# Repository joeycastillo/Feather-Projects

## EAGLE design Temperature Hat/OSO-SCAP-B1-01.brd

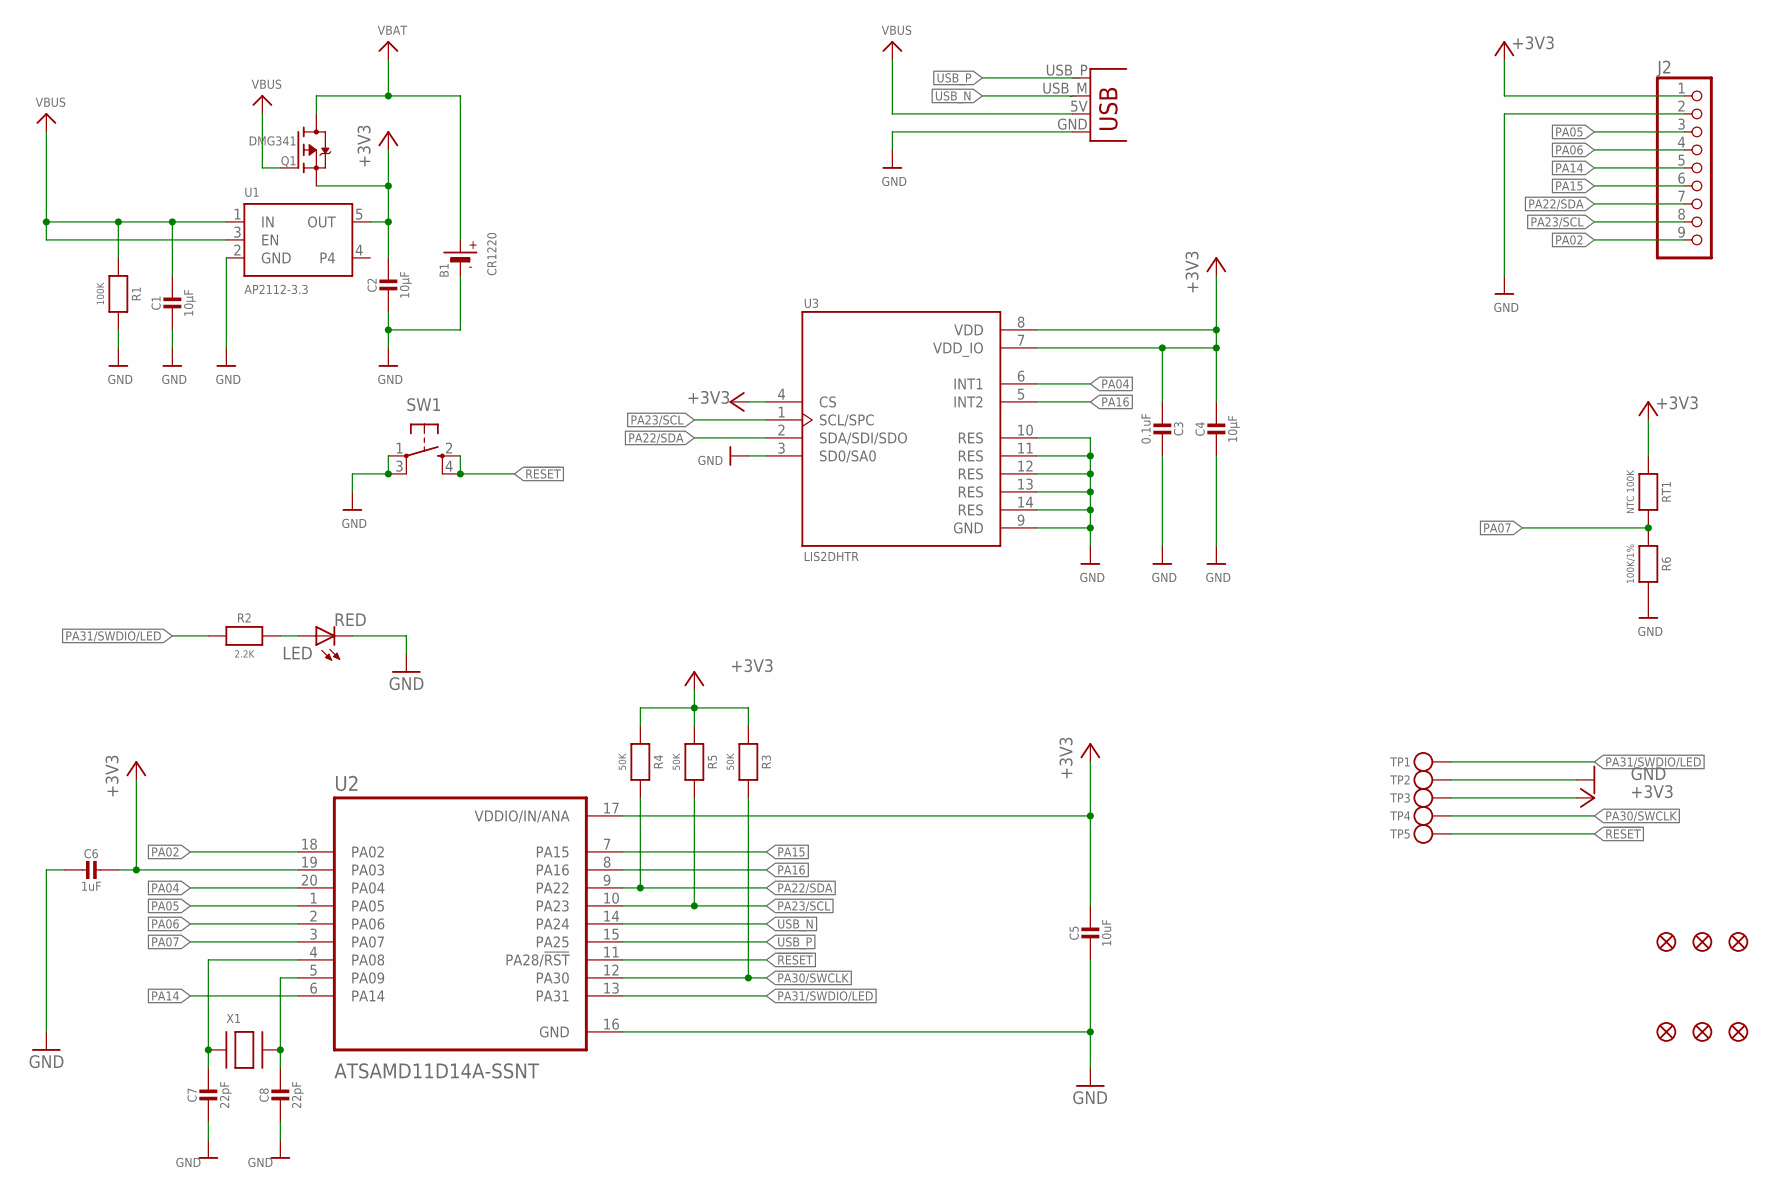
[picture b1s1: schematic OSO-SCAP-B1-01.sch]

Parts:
B1: CR1220
C1, C2, C4: 10µF; 0805-NO
C3: 0.1uF; 0805-NO
C5: 10uF; 0805-NO
C6: 1uF; 0805-NO
C7, C8: 22pF; 0805-NO
FID1, FID2, FID3, FID4, FID5, FID6: FIDUCIAL_1MM
J1: USBPCB; USB-A-PCB
J2: HEADER-1X9_JSTSH; JST_SH9
LED: RED; CHIP-LED0805
Q1: DMG341; SOT23-R
R1: 100K; 0805-NO
R2: 2.2K; 0805-NO
R3, R4, R5: 50K; 0805-NO
R6: 100K/1%; 0805-NO
RT1: NTC 100K; 0805-NO
SW1: SPST_TACT-KMR2; KMR2
TP1, TP2, TP3, TP4, TP5: TESTPOINTROUND2MMNO; TESTPOINT_ROUND_2MM_NO
U1: AP2112-3.3; SOT23-5
U2: ATSAMD11D14A-SSNT; SOIC127P1030X265-20N
U3: LIS2DHTR; PQFN35P200X200X100-14N
X1: XTAL-3.2X1.5; XTAL3215

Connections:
!RESET: SW1.2 (S), SW1.4 (S1), TP5.P$1, U2.11 (PA28/!RST)
+3V3: C2.1, C3.2, C4.1, C5.1, C6.1, J2.1, Q1.2 (S), R3.1, R4.1, R5.1, RT1.1, TP3.P$1, U1.5 (OUT), U2.17 (VDDIO/IN/ANA), U2.19 (PA03), U3.4 (CS), U3.7 (VDD_IO), U3.8 (VDD)
GND: B1.-, C1.2, C2.2, C3.1, C4.2, C5.2, C6.2, C7.2, C8.2, J1.GND, J2.2, LED.C, R1.2, R6.2, SW1.1, SW1.3 (P1), TP2.P$1, U1.2 (GND), U2.16 (GND), U3.3 (SD0/SA0), U3.9 (GND), U3.10 (RES), U3.11 (RES), U3.12 (RES), U3.13 (RES), U3.14 (RES)
unnamed: LED.A, R2.2
PA02: J2.9, U2.18 (PA02)
PA04: U2.20 (PA04), U3.6 (INT1)
PA05: J2.3, U2.1 (PA05)
PA06: J2.4, U2.2 (PA06)
PA07: R6.1, RT1.2, U2.3 (PA07)
PA14: J2.5, U2.6 (PA14)
PA15: J2.6, U2.7 (PA15)
PA16: U2.8 (PA16), U3.5 (INT2)
PA22/SDA: J2.7, R4.2, U2.9 (PA22), U3.2 (SDA/SDI/SDO)
PA23/SCL: J2.8, R5.2, U2.10 (PA23), U3.1 (SCL/SPC)
PA30/SWCLK: R3.2, TP4.P$1, U2.12 (PA30)
PA31/SWDIO/LED: R2.1, TP1.P$1, U2.13 (PA31)
USB_N: J1.USB_M (D-), U2.14 (PA24)
USB_P: J1.USB_P (D+), U2.15 (PA25)
VBAT: B1.+$1 (+), B1.+$2 (+), Q1.3 (D)
VBUS: C1.1, J1.5V (VBUS), Q1.1 (G), R1.1, U1.1 (IN), U1.3 (EN)
XIN32: C7.1, U2.4 (PA08), X1.P$1
XOUT32: C8.1, U2.5 (PA09), X1.P$2

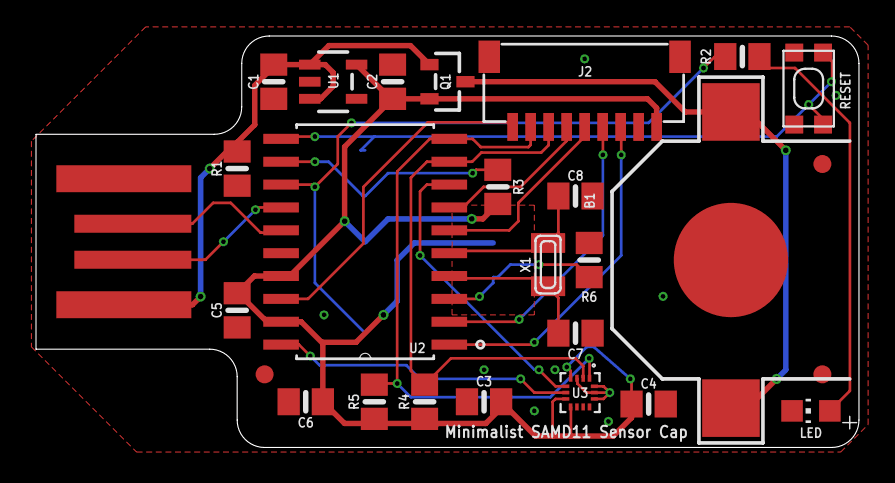
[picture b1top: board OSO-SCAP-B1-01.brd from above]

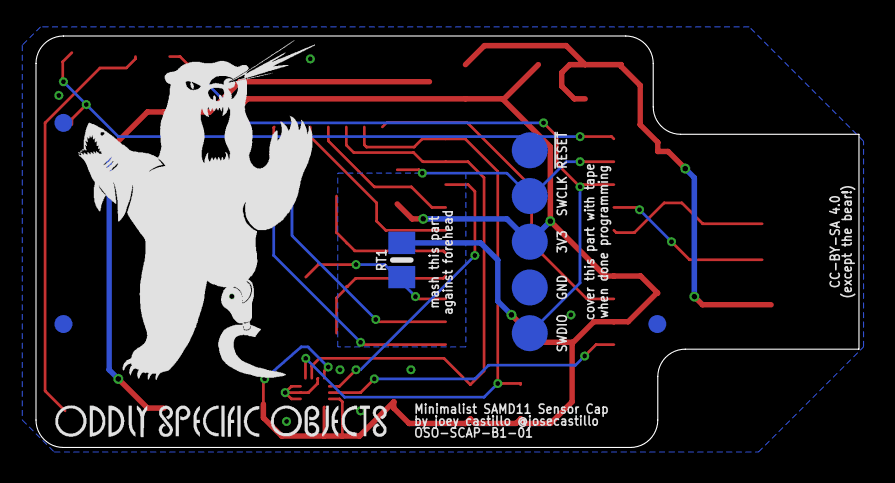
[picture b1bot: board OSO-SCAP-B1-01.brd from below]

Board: 2 copper layers, 45.7 x 22.9 mm, 38 parts (11 on the bottom side), 22 nets.

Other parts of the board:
U$16: OSO_BEAR_525X750MIL_1000DPI
U$21: OSO_WORDMARK_ONELINE_725MIL_1000DPI

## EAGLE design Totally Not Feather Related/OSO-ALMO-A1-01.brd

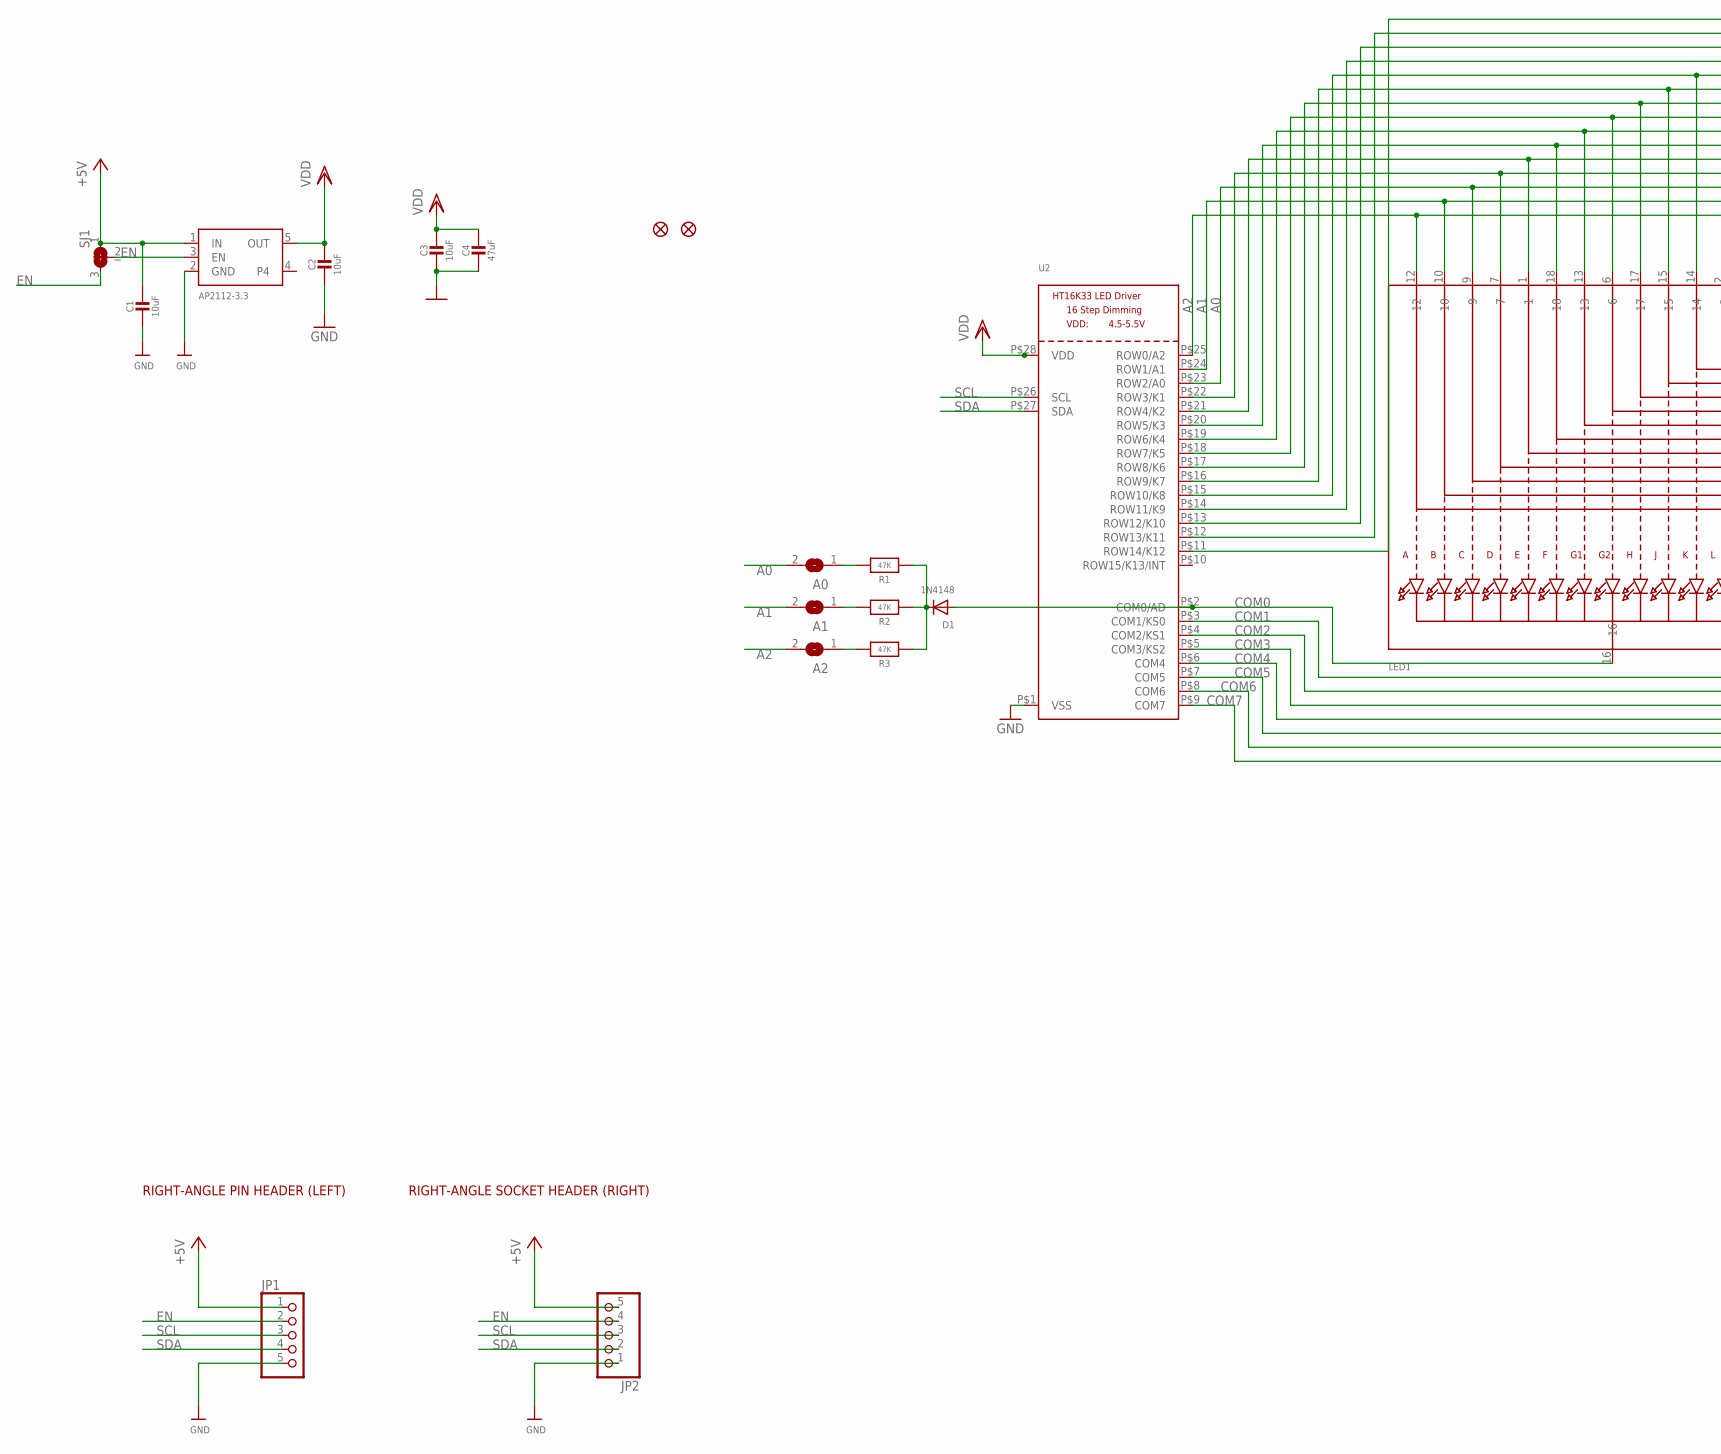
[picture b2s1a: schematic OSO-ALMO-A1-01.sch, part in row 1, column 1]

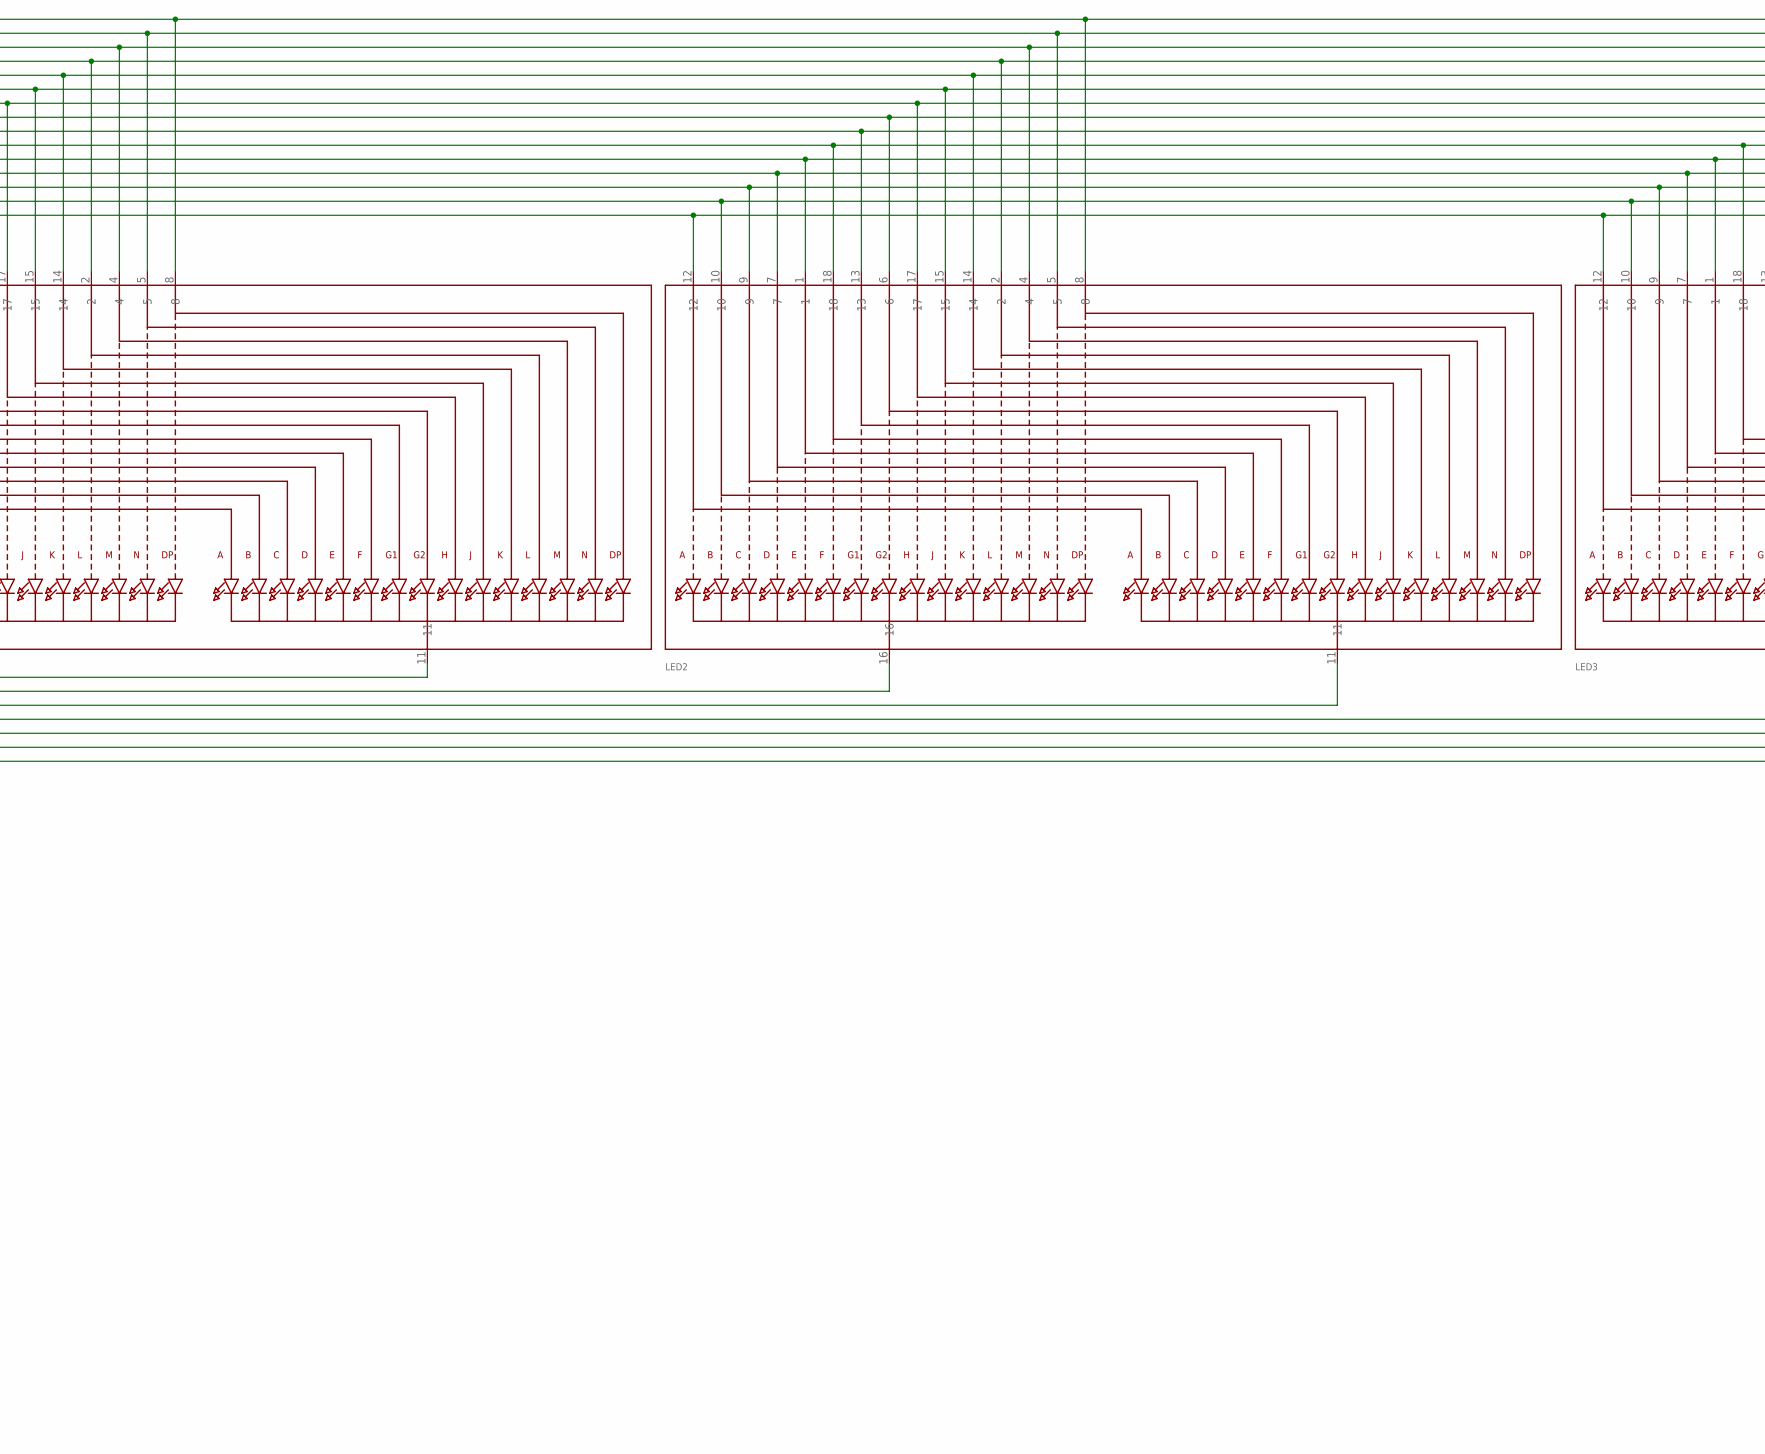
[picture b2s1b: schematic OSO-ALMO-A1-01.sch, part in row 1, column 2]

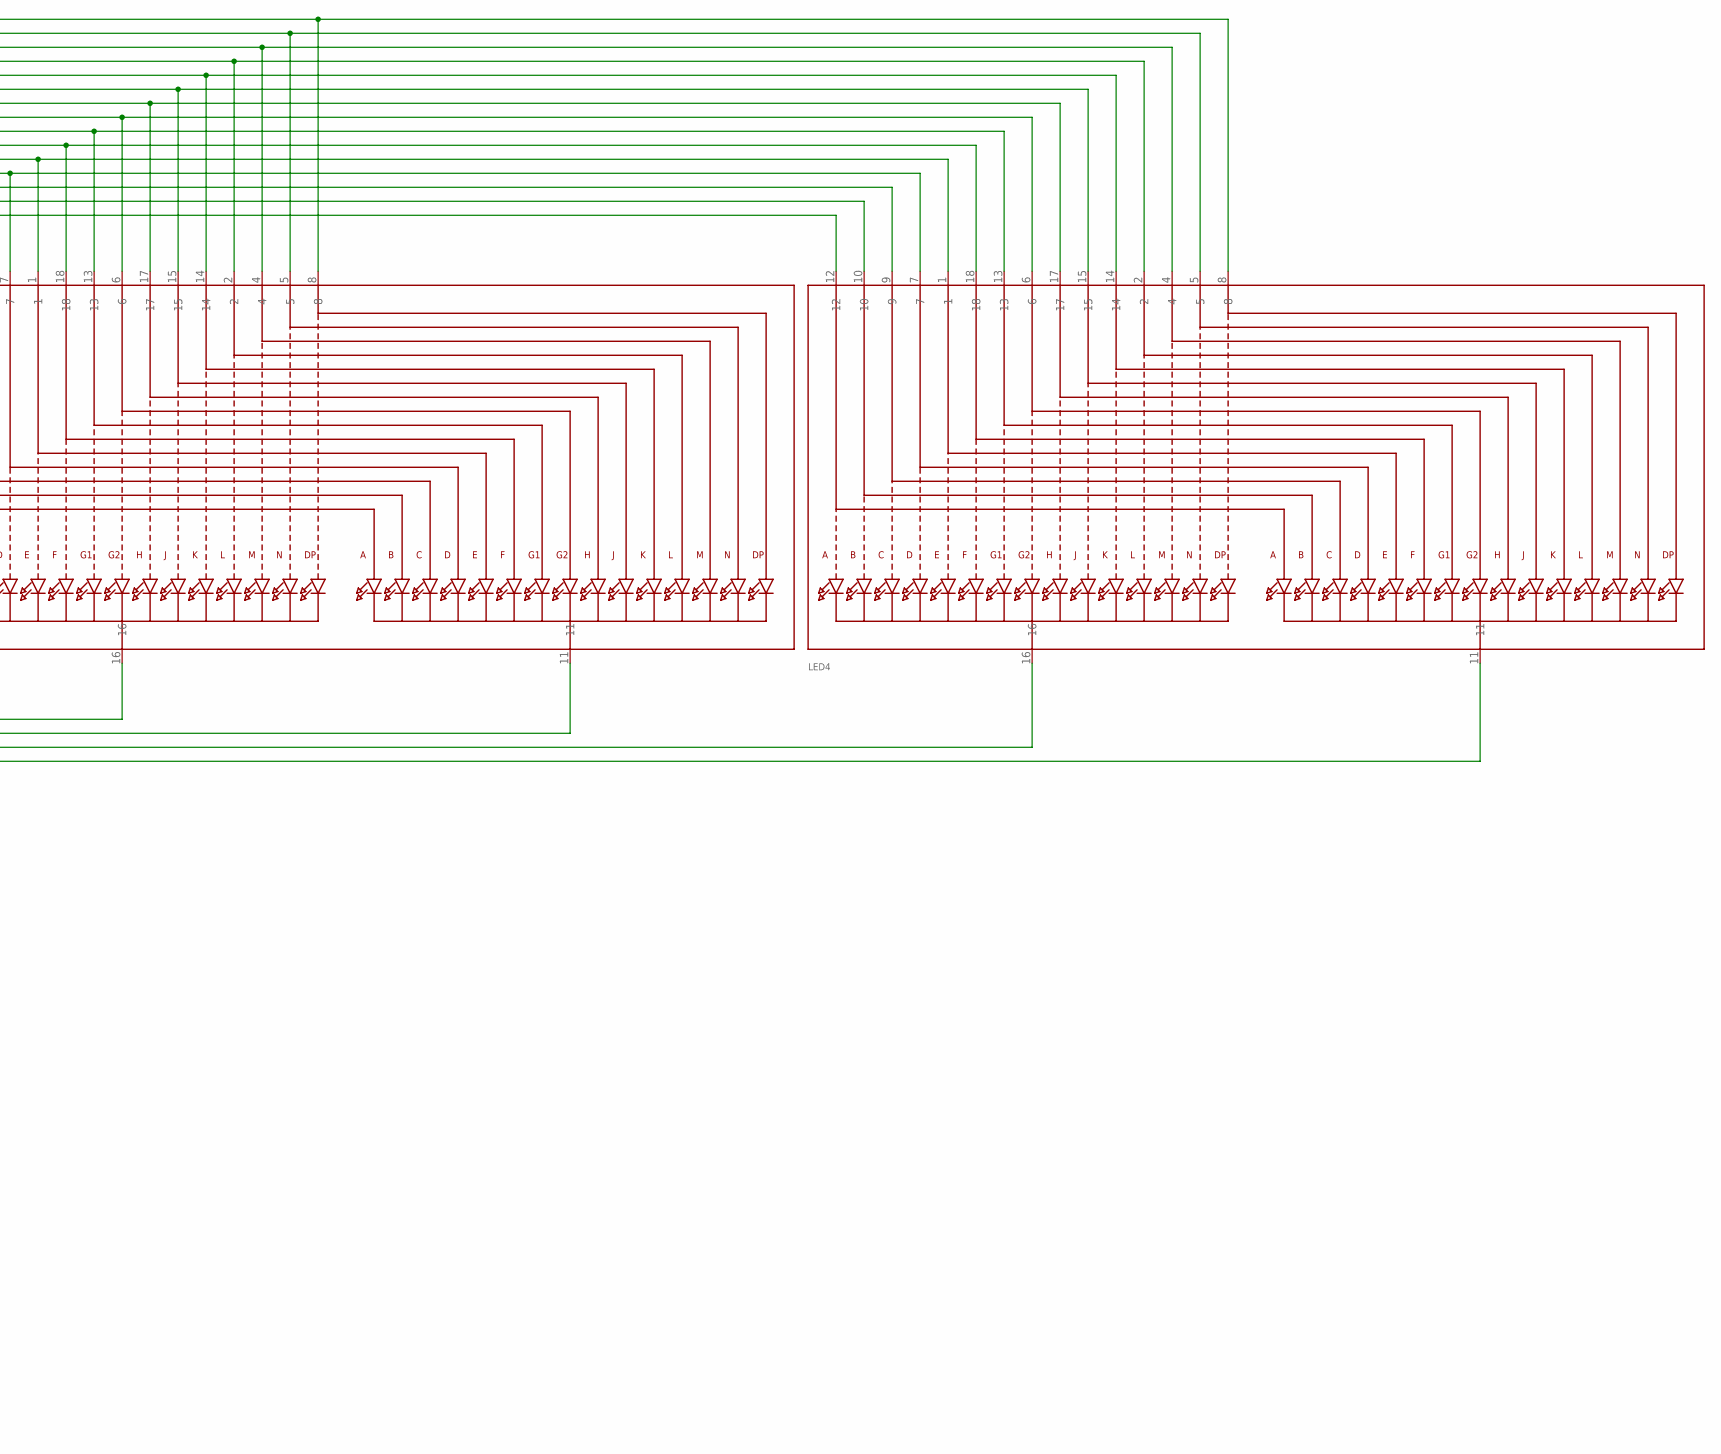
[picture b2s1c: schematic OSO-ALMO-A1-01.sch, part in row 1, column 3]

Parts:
A0, A1, A2: SOLDERJUMPERREFLOW_NOPASTE; SOLDERJUMPER_REFLOW_NOPASTE
C1, C2, C3: 10uF; 0805-NO
C4: 47uF; 0805-NO
D1: 1N4148; SOD-123FL
JP1, JP2: PINHD-1X5/90; 1X05/90
LED1, LED2, LED3, LED4: DISP_SEGMENT_STARBURST_DUAL_COMMONCATHODE; SEGMENT_STARTBUST_DUAL_KWA-541CBB
R1, R2, R3: 47K; 0805-NO
SJ1: SOLDERJUMPER_2WAY; SOLDERJUMPER_2WAY_OPEN_NOPASTE
U1: AP2112-3.3; SOT23-5
U2: HT16K33_SOP28_SKINNY; SOP28_300MIL_SKINNY
U$1, U$2: FIDUCIAL""; FIDUCIAL_1MM

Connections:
+5V: C1.1, JP1.1, JP2.5, SJ1.1, U1.1 (IN)
A0: A0.2, LED1.9, LED2.9, LED3.9, LED4.9, U2.P$23 (ROW2/A0)
A1: A1.2, LED1.10, LED2.10, LED3.10, LED4.10, U2.P$24 (ROW1/A1)
A2: A2.2, LED1.12, LED2.12, LED3.12, LED4.12, U2.P$25 (ROW0/A2)
COM0: D1.A, LED1.16, U2.P$2 (COM0/AD)
COM1: LED1.11, U2.P$3 (COM1/KS0)
COM2: LED2.16, U2.P$4 (COM2/KS1)
COM3: LED2.11, U2.P$5 (COM3/KS2)
COM4: LED3.16, U2.P$6 (COM4)
COM5: LED3.11, U2.P$7 (COM5)
COM6: LED4.16, U2.P$8 (COM6)
COM7: LED4.11, U2.P$9 (COM7)
EN: JP1.2, JP2.4, SJ1.3
GND: C1.2, C2.2, C3.2, C4.2, JP1.5, JP2.1, U1.2 (GND), U2.P$1 (VSS)
unnamed: D1.C, R1.1, R2.1, R3.1
unnamed: LED1.17, LED2.17, LED3.17, LED4.17, U2.P$17 (ROW8/K6)
unnamed: LED1.15, LED2.15, LED3.15, LED4.15, U2.P$16 (ROW9/K7)
unnamed: LED1.14, LED2.14, LED3.14, LED4.14, U2.P$15 (ROW10/K8)
unnamed: A2.1, R3.2
unnamed: LED1.2, LED2.2, LED3.2, LED4.2, U2.P$14 (ROW11/K9)
unnamed: LED1.4, LED2.4, LED3.4, LED4.4, U2.P$13 (ROW12/K10)
unnamed: LED1.7, LED2.7, LED3.7, LED4.7, U2.P$22 (ROW3/K1)
unnamed: LED1.1, LED2.1, LED3.1, LED4.1, U2.P$21 (ROW4/K2)
unnamed: LED1.18, LED2.18, LED3.18, LED4.18, U2.P$20 (ROW5/K3)
unnamed: LED1.13, LED2.13, LED3.13, LED4.13, U2.P$19 (ROW6/K4)
unnamed: LED1.5, LED2.5, LED3.5, LED4.5, U2.P$12 (ROW13/K11)
unnamed: LED1.8, LED2.8, LED3.8, LED4.8, U2.P$11 (ROW14/K12)
unnamed: LED1.6, LED2.6, LED3.6, LED4.6, U2.P$18 (ROW7/K5)
unnamed: A1.1, R2.2
unnamed: A0.1, R1.2
SCL: JP1.3, JP2.3, U2.P$26 (SCL)
SDA: JP1.4, JP2.2, U2.P$27 (SDA)
VDD: C2.1, C3.1, C4.1, U1.5 (OUT), U2.P$28 (VDD)
_EN: SJ1.2, U1.3 (EN)

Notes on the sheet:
RIGHT-ANGLE PIN HEADER (LEFT)
RIGHT-ANGLE SOCKET HEADER (RIGHT)

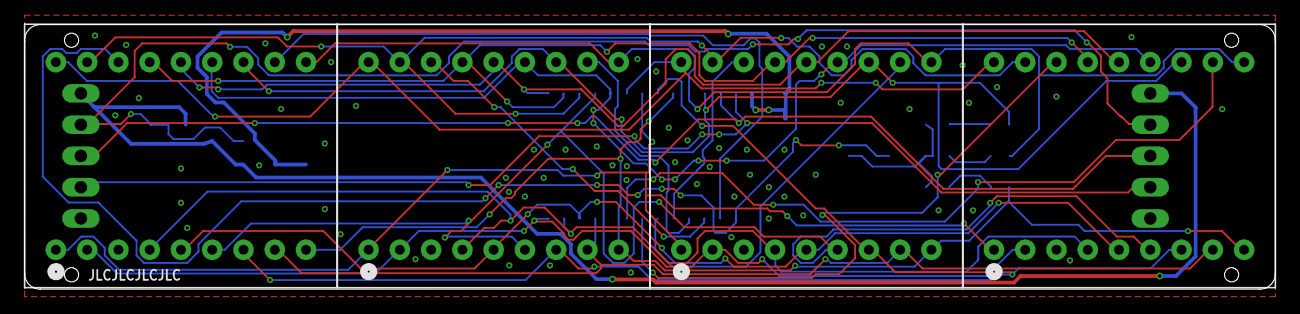
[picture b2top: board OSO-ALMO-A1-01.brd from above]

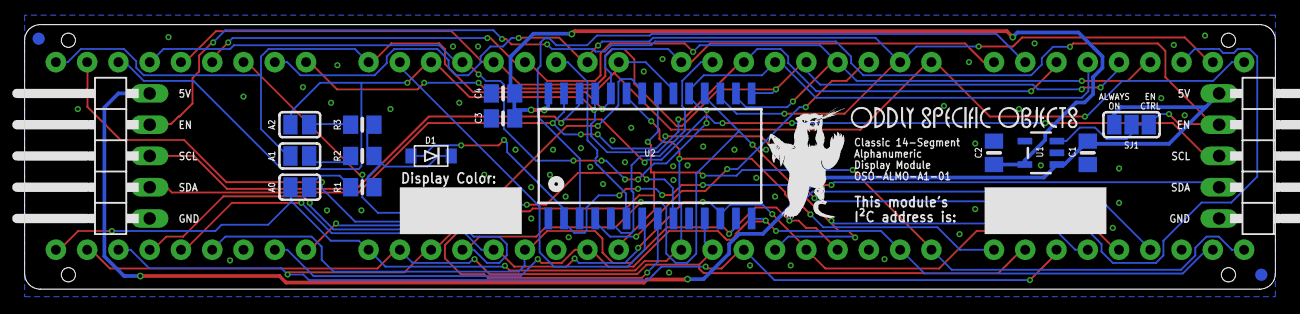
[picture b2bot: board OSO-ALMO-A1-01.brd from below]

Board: 2 copper layers, 101.6 x 21.5 mm, 24 parts (20 on the bottom side), 34 nets.

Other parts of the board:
U$3: OSO_WORDMARK_ONELINE_725MIL_1000DPI
U$6: OSO_BEAR_250X360MIL_1000DPI

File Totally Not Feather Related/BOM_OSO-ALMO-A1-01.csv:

"Qty";"Value";"Device";"Package";"Parts";"Description";"BOM";
"4";"";"DISP_SEGMENT_STARBURST_DUAL_COMMONCATHODE";"SEGMENT_STARTBUST_DUAL_KWA-541CBB";"LED1, LED2, LED3, LED4";"2 x Starburst Segment Displays - Common Cathode";"";
"1";"";"HT16K33_SOP28_SKINNY";"SOP28_300MIL_SKINNY";"U2";"";"";
"2";"";"PINHD-1X5/90";"1X05/90";"JP1, JP2";"PIN HEADER";"";
"3";"";"SOLDERJUMPERREFLOW_NOPASTE";"SOLDERJUMPER_REFLOW_NOPASTE";"A0, A1, A2";"SMD Solder JUMPER";"";
"1";"";"SOLDERJUMPER_2WAY";"SOLDERJUMPER_2WAY_OPEN_NOPASTE";"SJ1";"2-Way Solder Jumper";"";
"3";"10uF";"CAP_CERAMIC0805-NOOUTLINE";"0805-NO";"C1, C2, C3";"Ceramic Capacitors";"";
"1";"1N4148";"DIODE_SOD-123FL";"SOD-123FL";"D1";"Diode";"";
"3";"47K";"RESISTOR0805_NOOUTLINE";"0805-NO";"R1, R2, R3";"Resistors";"";
"1";"47uF";"CAP_CERAMIC0805-NOOUTLINE";"0805-NO";"C4";"Ceramic Capacitors";"";
"1";"AP2112-3.3";"VREG_SOT23-5";"SOT23-5";"U1";"SOT23-5 Fixed Voltage Regulators";"";
"2";"FIDUCIAL""";"FIDUCIAL""";"FIDUCIAL_1MM";"U$1, U$2";"Fiducial Alignment Points";"EXCLUDE";

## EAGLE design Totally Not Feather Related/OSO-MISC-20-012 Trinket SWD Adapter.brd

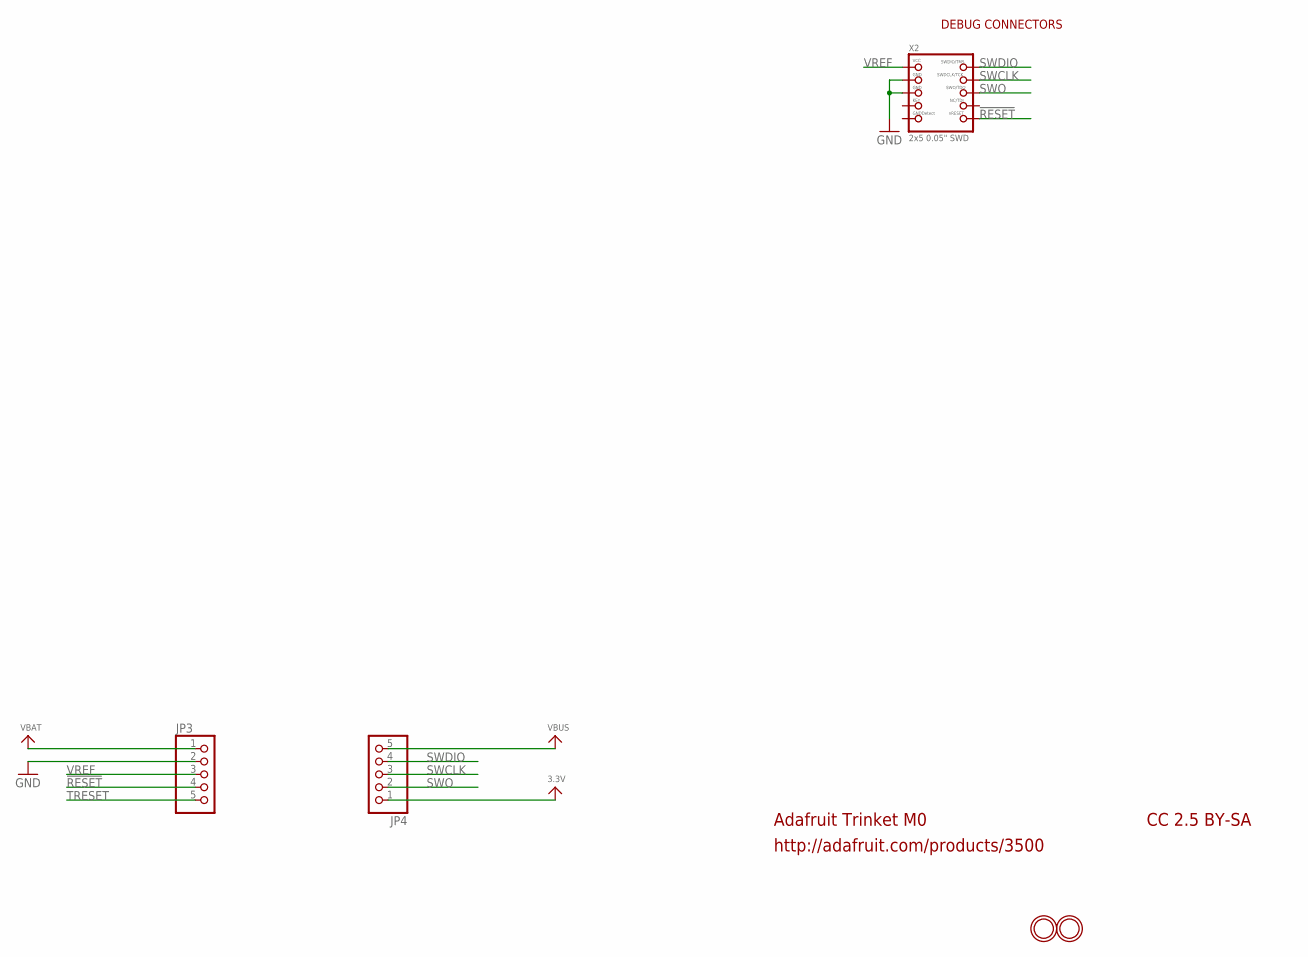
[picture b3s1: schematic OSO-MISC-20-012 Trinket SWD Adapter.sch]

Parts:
JP3, JP4: HEADER-1X576MIL; 1X05_ROUND_76
U$8, U$9: MOUNTINGHOLE2.0; MOUNTINGHOLE_2.0_PLATED
X2: 2x5 0.05" SWD; 2X05_1.27MM_BOX_POSTS

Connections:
3.3V: JP4.1
!RESET: JP3.4, X2.10 (NRESET)
GND: JP3.2, X2.3 (GND), X2.5 (GND)
SWCLK: JP4.3, X2.4 (SWDCLK)
SWDIO: JP4.4, X2.2 (SWDIO)
SWO: JP4.2, X2.6 (SWO)
TRESET: JP3.5
VBAT: JP3.1
VBUS: JP4.5
VREF: JP3.3, X2.1 (VCC)

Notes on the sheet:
Adafruit Trinket M0
http://adafruit.com/products/3500
CC 2.5 BY-SA
DEBUG CONNECTORS

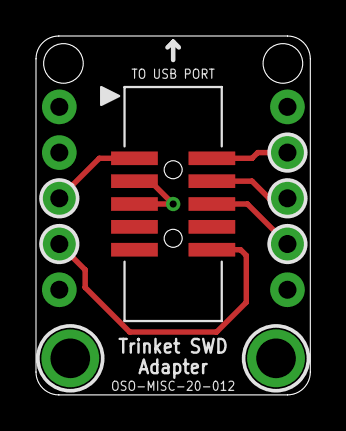
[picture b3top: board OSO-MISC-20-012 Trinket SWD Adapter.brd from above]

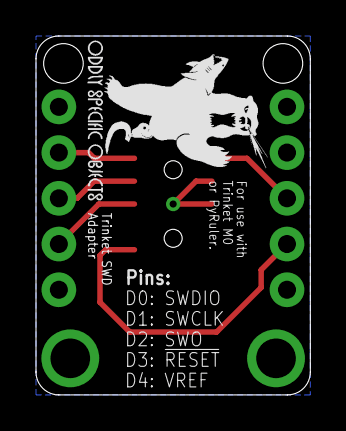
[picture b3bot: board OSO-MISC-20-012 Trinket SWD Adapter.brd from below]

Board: 2 copper layers, 15.2 x 19.9 mm, 7 parts (2 on the bottom side), 6 nets.

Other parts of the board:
U$1: OSO_BEAR_250X360MIL_1000DPI
U$2: OSO_WORDMARK_ONELINE_350MIL_1000DPI

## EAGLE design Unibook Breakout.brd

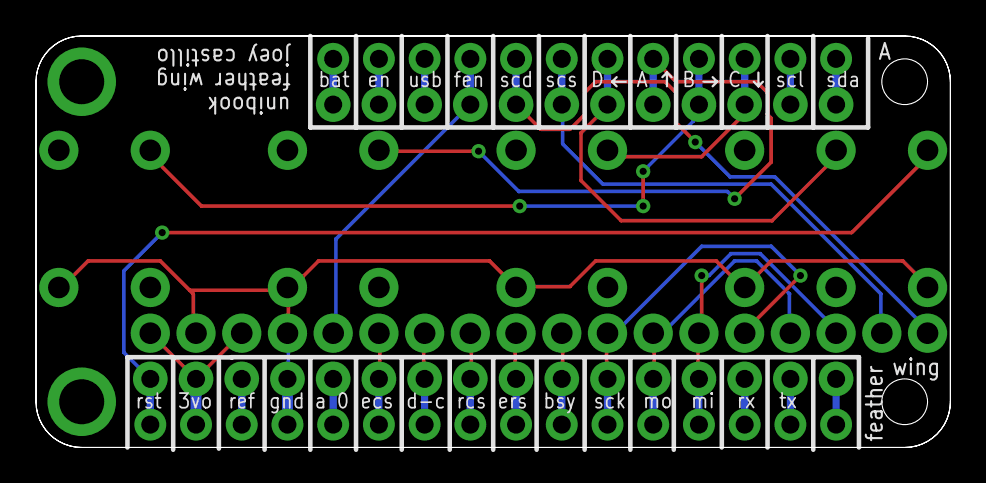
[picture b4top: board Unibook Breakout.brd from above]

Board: 2 copper layers, 50.8 x 22.9 mm, 3 parts (0 on the bottom side), 28 nets.

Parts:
JP1: 1X12_ROUND_76MIL
JP3: 1X16_ROUND_76MIL
MS1: FEATHERWING

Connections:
3V: JP3.15, MS1.2
AREF: JP3.14, MS1.3
GND: JP3.13, MS1.4
unnamed: JP1.2, MS1.27
unnamed: JP3.1, MS1.16
unnamed: JP1.4, MS1.25
unnamed: JP3.2, MS1.15
unnamed: JP1.5, MS1.24
unnamed: JP3.3, MS1.14
unnamed: JP3.4, MS1.13
unnamed: JP3.5, MS1.12
unnamed: JP3.6, MS1.11
unnamed: JP3.7, MS1.10
unnamed: JP3.8, MS1.9
unnamed: JP3.9, MS1.8
unnamed: JP3.10, MS1.7
unnamed: JP3.11, MS1.6
unnamed: JP3.12, MS1.5
unnamed: JP3.16, MS1.1
unnamed: JP1.6, MS1.23
unnamed: JP1.7, MS1.22
unnamed: JP1.8, MS1.21
unnamed: JP1.9, MS1.20
unnamed: JP1.10, MS1.19
unnamed: JP1.11, MS1.18
unnamed: JP1.12, MS1.17
USB: JP1.3, MS1.26
VBAT: JP1.1, MS1.28

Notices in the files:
Temperature Hat/OSO-SCAP-B1-01.brd:
CC-BY-SA 4.0
parts and their libraries:
microbuilder: This work is placed in the public domain, and may be freely used for commercial and non-commercial work with the following conditions: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
My Stuff: cc-by-sa 3.0
